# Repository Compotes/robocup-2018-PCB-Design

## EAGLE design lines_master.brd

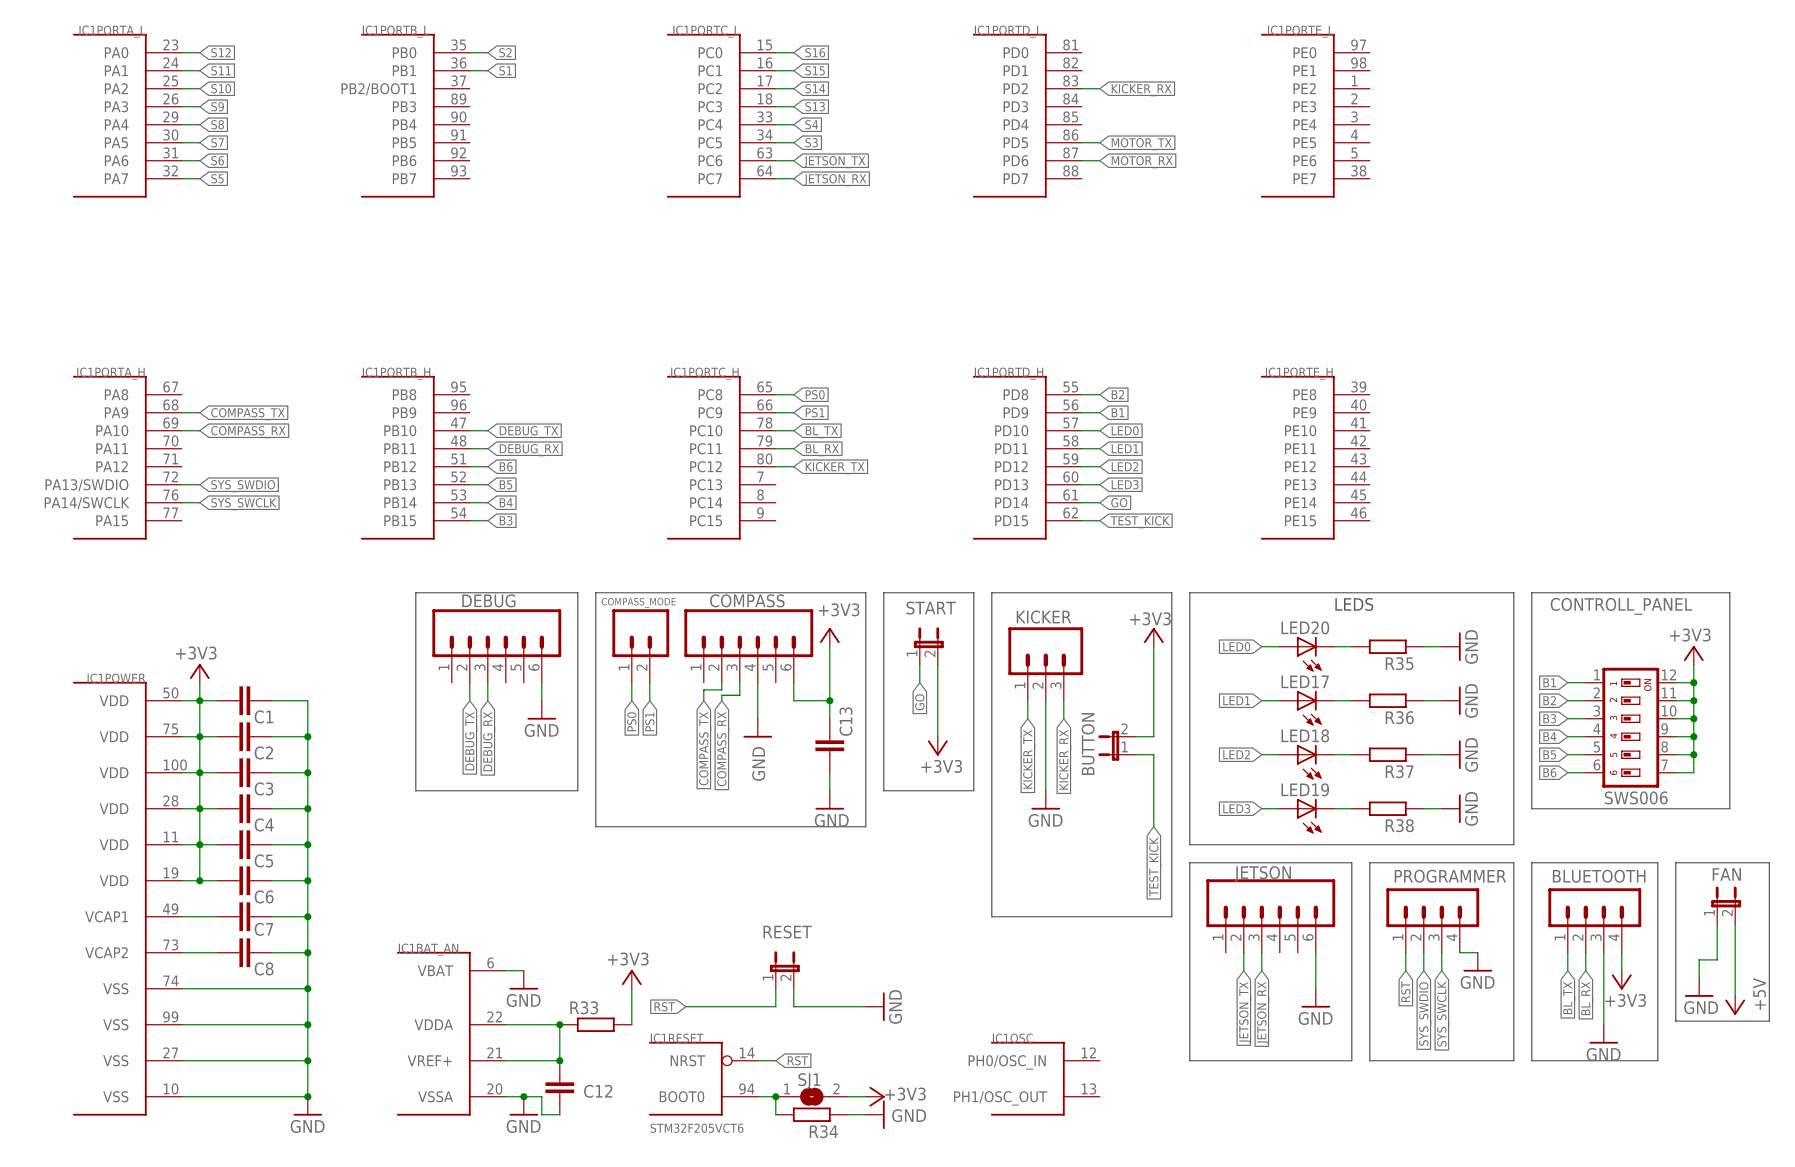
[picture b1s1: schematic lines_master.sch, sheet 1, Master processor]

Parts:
BLUETOOTH: MA04-1
BUTTON: JP1E; JP1
C1, C2, C3, C4, C5, C6, C12, C13: 100K; C0603
C7, C8: 2M2; C0805
COMPASS: M06; 06P
COMPASS_MODE: M02; 02P
CONTROLL_PANEL: SWS006; SMS-006
DEBUG: M06; 06P
FAN: JP1E; JP1
IC1: STM32F205VCT6; TQFP100
JETSON: M06; 06P
KICKER: M03; 03P
LED17, LED18, LED19, LED20: LED_E; LED_1206
PROGRAMMER: MA04-1
R33: R-EU_R1206; R1206
R34, R35, R36, R37, R38: R-EU_R0603; R0603
RESET: JP1E; JP1
SJ1: SJ
START: JP1E; JP1

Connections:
+3V3: BLUETOOTH.4, BUTTON.2, C1.2, C2.2, C3.2, C4.2, C5.2, C6.2, C13.1, COMPASS.6, CONTROLL_PANEL.7, CONTROLL_PANEL.8, CONTROLL_PANEL.9, CONTROLL_PANEL.10, CONTROLL_PANEL.11, CONTROLL_PANEL.12, IC1.11 (VDD), IC1.19 (VDD), IC1.28 (VDD), IC1.50 (VDD), IC1.75 (VDD), IC1.100 (VDD), R33.2, SJ1.2, START.2; also elsewhere on the board
+5V: FAN.2; also elsewhere on the board
B1: CONTROLL_PANEL.1, IC1.56 (PD9)
B2: CONTROLL_PANEL.2, IC1.55 (PD8)
B3: CONTROLL_PANEL.3, IC1.54 (PB15)
B4: CONTROLL_PANEL.4, IC1.53 (PB14)
B5: CONTROLL_PANEL.5, IC1.52 (PB13)
B6: CONTROLL_PANEL.6, IC1.51 (PB12)
BL_RX: BLUETOOTH.2, IC1.79 (PC11)
BL_TX: BLUETOOTH.1, IC1.78 (PC10)
COMPASS_RX: COMPASS.3, IC1.69 (PA10)
COMPASS_TX: COMPASS.2, IC1.68 (PA9)
DEBUG_RX: DEBUG.3, IC1.48 (PB11)
DEBUG_TX: DEBUG.2, IC1.47 (PB10)
GND: BLUETOOTH.3, C1.1, C2.1, C3.1, C4.1, C5.1, C6.1, C7.1, C8.1, C12.2, C13.2, COMPASS.4, DEBUG.6, FAN.1, IC1.6 (VBAT), IC1.10 (VSS), IC1.20 (VSSA), IC1.27 (VSS), IC1.74 (VSS), IC1.99 (VSS), JETSON.6, KICKER.2, PROGRAMMER.4, R34.1, R35.1, R36.1, R37.1, R38.1, RESET.2; also elsewhere on the board
GO: IC1.61 (PD14), START.1
JETSON_RX: IC1.64 (PC7), JETSON.3
JETSON_TX: IC1.63 (PC6), JETSON.2
KICKER_RX: IC1.83 (PD2), KICKER.3
KICKER_TX: IC1.80 (PC12), KICKER.1
LED0: IC1.57 (PD10), LED20.A
LED1: IC1.58 (PD11), LED17.A
LED2: IC1.59 (PD12), LED18.A
LED3: IC1.60 (PD13), LED19.A
MOTOR_RX: IC1.87 (PD6); also elsewhere on the board
MOTOR_TX: IC1.86 (PD5); also elsewhere on the board
unnamed: C7.2, IC1.49 (VCAP1)
unnamed: C8.2, IC1.73 (VCAP2)
unnamed: C12.1, IC1.21 (VREF+), IC1.22 (VDDA), R33.1
unnamed: IC1.94 (BOOT0), R34.2, SJ1.1
unnamed: LED20.C, R35.2
unnamed: LED17.C, R36.2
unnamed: LED18.C, R37.2
unnamed: LED19.C, R38.2
PS0: COMPASS_MODE.1, IC1.65 (PC8)
PS1: COMPASS_MODE.2, IC1.66 (PC9)
RST: IC1.14 (NRST), PROGRAMMER.1, RESET.1
S1: IC1.36 (PB1); also elsewhere on the board
S2: IC1.35 (PB0); also elsewhere on the board
S3: IC1.34 (PC5); also elsewhere on the board
S4: IC1.33 (PC4); also elsewhere on the board
S5: IC1.32 (PA7); also elsewhere on the board
S6: IC1.31 (PA6); also elsewhere on the board
S7: IC1.30 (PA5); also elsewhere on the board
S8: IC1.29 (PA4); also elsewhere on the board
S9: IC1.26 (PA3); also elsewhere on the board
S10: IC1.25 (PA2); also elsewhere on the board
S11: IC1.24 (PA1); also elsewhere on the board
S12: IC1.23 (PA0); also elsewhere on the board
S13: IC1.18 (PC3); also elsewhere on the board
S14: IC1.17 (PC2); also elsewhere on the board
S15: IC1.16 (PC1); also elsewhere on the board
S16: IC1.15 (PC0); also elsewhere on the board
SYS_SWCLK: IC1.76 (PA14/SWCLK), PROGRAMMER.3
SYS_SWDIO: IC1.72 (PA13/SWDIO), PROGRAMMER.2
TEST_KICK: BUTTON.1, IC1.62 (PD15)

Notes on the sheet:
LEDS

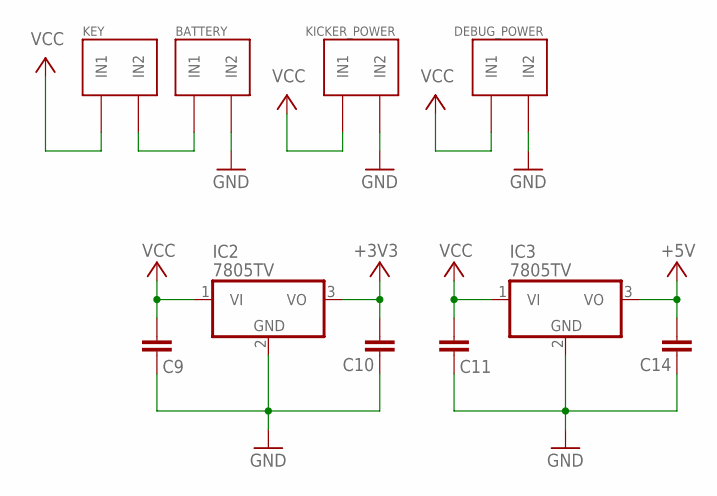
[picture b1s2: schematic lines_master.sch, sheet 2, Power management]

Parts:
BATTERY: MOTOR_CONNECTOR
C9, C10, C11, C14: 100K; C0603
DEBUG_POWER: MOTOR_CONNECTOR
IC2, IC3: 7805TV; TO220V
KEY: MOTOR_CONNECTOR
KICKER_POWER: MOTOR_CONNECTOR

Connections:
+3V3: C10.2, IC2.3 (VO); also elsewhere on the board
+5V: C14.2, IC3.3 (VO); also elsewhere on the board
GND: BATTERY.IN2, C9.1, C10.1, C11.1, C14.1, DEBUG_POWER.IN2, IC2.2 (GND), IC3.2 (GND), KICKER_POWER.IN2; also elsewhere on the board
unnamed: BATTERY.IN1, KEY.IN2
VCC: C9.2, C11.2, DEBUG_POWER.IN1, IC2.1 (VI), IC3.1 (VI), KEY.IN1, KICKER_POWER.IN1; also elsewhere on the board

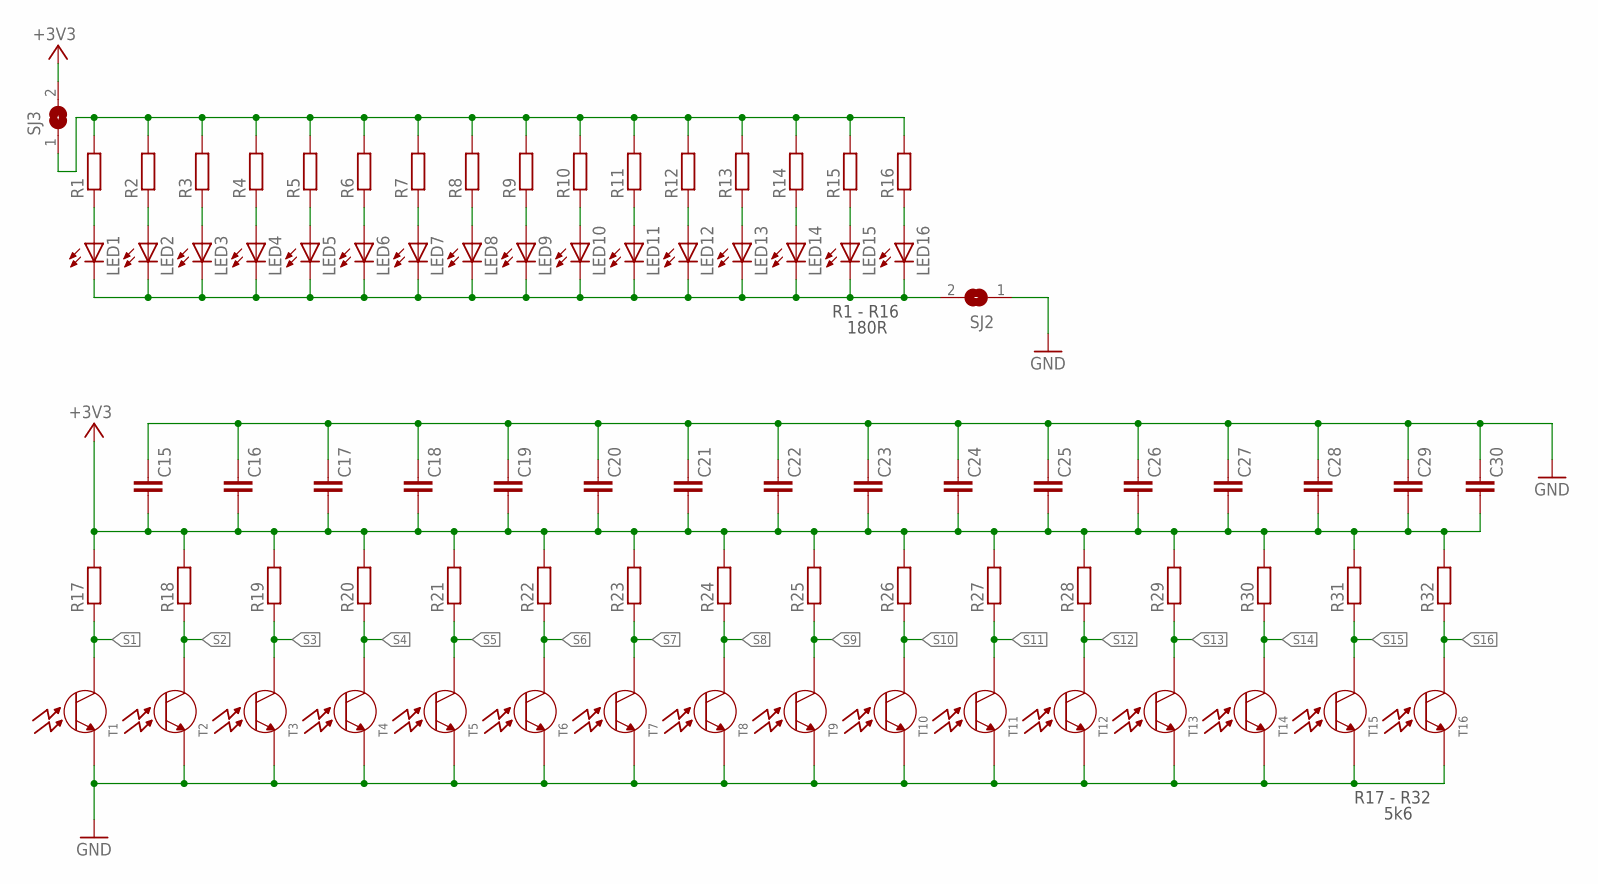
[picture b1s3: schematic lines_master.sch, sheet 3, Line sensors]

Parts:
C15, C16, C17, C18, C19, C20, C21, C22, C23, C24, C25, C26, C27, C28, C29, C30: 100K; C0603
LED1, LED2, LED3, LED4, LED5, LED6, LED7, LED8, LED9, LED10, LED11, LED12, LED13, LED14, LED15, LED16: LEDKA-3528ASYC; KA-3528ASYC
R1, R2, R3, R4, R5, R6, R7, R8, R9, R10, R11, R12, R13, R14, R15, R16: 180R; R0603
R17, R18, R19, R20, R21, R22, R23, R24, R25, R26, R27, R28, R29, R30, R31, R32: 5K6; R0603
SJ2, SJ3: SJ
T1, T2, T3, T4, T5, T6, T7, T8, T9, T10, T11, T12, T13, T14, T15, T16: LL-S150-1A; LL-S150PTC-1A

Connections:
+3V3: C15.2, C16.2, C17.2, C18.2, C19.2, C20.2, C21.2, C22.2, C23.2, C24.2, C25.2, C26.2, C27.2, C28.2, C29.2, C30.2, R17.2, R18.2, R19.2, R20.2, R21.2, R22.2, R23.2, R24.2, R25.2, R26.2, R27.2, R28.2, R29.2, R30.2, R31.2, R32.2, SJ3.2; also elsewhere on the board
GND: C15.1, C16.1, C17.1, C18.1, C19.1, C20.1, C21.1, C22.1, C23.1, C24.1, C25.1, C26.1, C27.1, C28.1, C29.1, C30.1, SJ2.1, T1.E, T2.E, T3.E, T4.E, T5.E, T6.E, T7.E, T8.E, T9.E, T10.E, T11.E, T12.E, T13.E, T14.E, T15.E, T16.E; also elsewhere on the board
unnamed: LED1.A, R1.1
unnamed: LED2.A, R2.1
unnamed: LED3.A, R3.1
unnamed: LED4.A, R4.1
unnamed: LED5.A, R5.1
unnamed: LED6.A, R6.1
unnamed: LED7.A, R7.1
unnamed: LED8.A, R8.1
unnamed: LED9.A, R9.1
unnamed: LED10.A, R10.1
unnamed: LED11.A, R11.1
unnamed: LED12.A, R12.1
unnamed: LED13.A, R13.1
unnamed: LED14.A, R14.1
unnamed: LED15.A, R15.1
unnamed: LED16.A, R16.1
unnamed: LED1.C, LED2.C, LED3.C, LED4.C, LED5.C, LED6.C, LED7.C, LED8.C, LED9.C, LED10.C, LED11.C, LED12.C, LED13.C, LED14.C, LED15.C, LED16.C, SJ2.2
unnamed: R1.2, R2.2, R3.2, R4.2, R5.2, R6.2, R7.2, R8.2, R9.2, R10.2, R11.2, R12.2, R13.2, R14.2, R15.2, R16.2, SJ3.1
S1: R17.1, T1.C; also elsewhere on the board
S2: R18.1, T2.C; also elsewhere on the board
S3: R19.1, T3.C; also elsewhere on the board
S4: R20.1, T4.C; also elsewhere on the board
S5: R21.1, T5.C; also elsewhere on the board
S6: R22.1, T6.C; also elsewhere on the board
S7: R23.1, T7.C; also elsewhere on the board
S8: R24.1, T8.C; also elsewhere on the board
S9: R25.1, T9.C; also elsewhere on the board
S10: R26.1, T10.C; also elsewhere on the board
S11: R27.1, T11.C; also elsewhere on the board
S12: R28.1, T12.C; also elsewhere on the board
S13: R29.1, T13.C; also elsewhere on the board
S14: R30.1, T14.C; also elsewhere on the board
S15: R31.1, T15.C; also elsewhere on the board
S16: R32.1, T16.C; also elsewhere on the board

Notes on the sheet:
R1 - R16 180R
R17 - R32 5k6

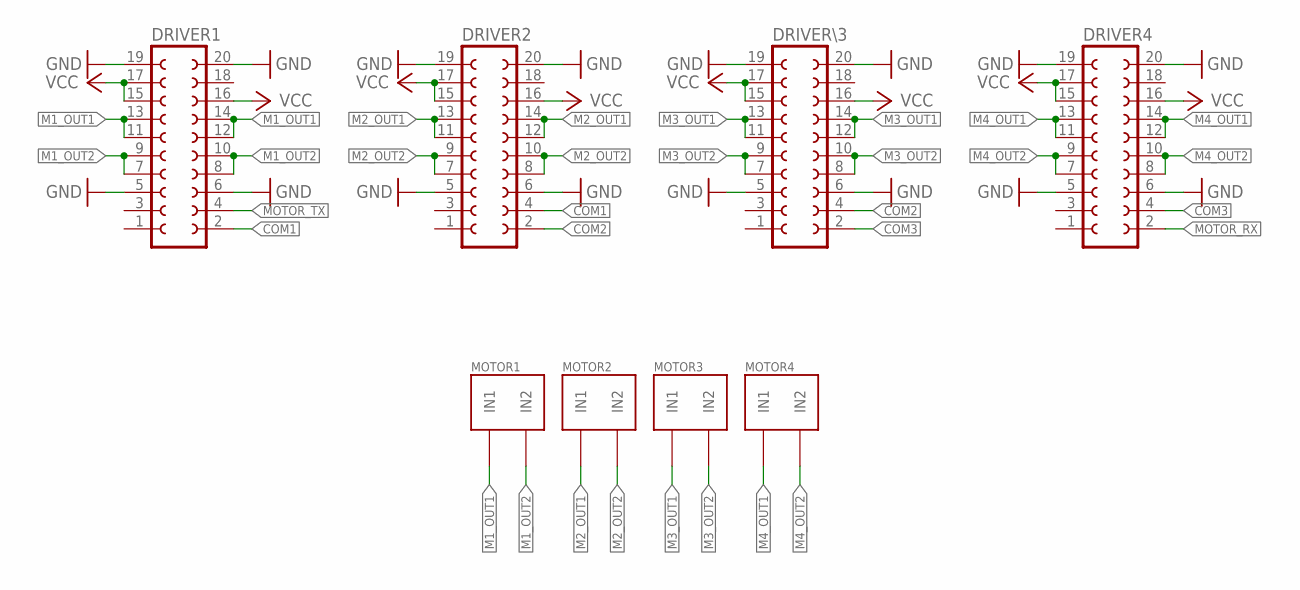
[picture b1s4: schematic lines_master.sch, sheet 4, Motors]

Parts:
DRIVER1, DRIVER2, DRIVER4: FE10-2
DRIVER\3: FE10-2
MOTOR1, MOTOR2, MOTOR3, MOTOR4: MOTOR_CONNECTOR

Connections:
COM1: DRIVER1.2, DRIVER2.4
COM2: DRIVER2.2, DRIVER\3.4
COM3: DRIVER4.4, DRIVER\3.2
GND: DRIVER1.5, DRIVER1.6, DRIVER1.19, DRIVER1.20, DRIVER2.5, DRIVER2.6, DRIVER2.19, DRIVER2.20, DRIVER4.5, DRIVER4.6, DRIVER4.19, DRIVER4.20, DRIVER\3.5, DRIVER\3.6, DRIVER\3.19, DRIVER\3.20; also elsewhere on the board
M1_OUT1: DRIVER1.11, DRIVER1.12, DRIVER1.13, DRIVER1.14, MOTOR1.IN1
M1_OUT2: DRIVER1.7, DRIVER1.8, DRIVER1.9, DRIVER1.10, MOTOR1.IN2
M2_OUT1: DRIVER2.11, DRIVER2.12, DRIVER2.13, DRIVER2.14, MOTOR2.IN1
M2_OUT2: DRIVER2.7, DRIVER2.8, DRIVER2.9, DRIVER2.10, MOTOR2.IN2
M3_OUT1: DRIVER\3.11, DRIVER\3.12, DRIVER\3.13, DRIVER\3.14, MOTOR3.IN1
M3_OUT2: DRIVER\3.7, DRIVER\3.8, DRIVER\3.9, DRIVER\3.10, MOTOR3.IN2
M4_OUT1: DRIVER4.11, DRIVER4.12, DRIVER4.13, DRIVER4.14, MOTOR4.IN1
M4_OUT2: DRIVER4.7, DRIVER4.8, DRIVER4.9, DRIVER4.10, MOTOR4.IN2
MOTOR_RX: DRIVER4.2; also elsewhere on the board
MOTOR_TX: DRIVER1.4; also elsewhere on the board
VCC: DRIVER1.15, DRIVER1.16, DRIVER1.17, DRIVER2.15, DRIVER2.16, DRIVER2.17, DRIVER4.15, DRIVER4.16, DRIVER4.17, DRIVER\3.15, DRIVER\3.16, DRIVER\3.17; also elsewhere on the board

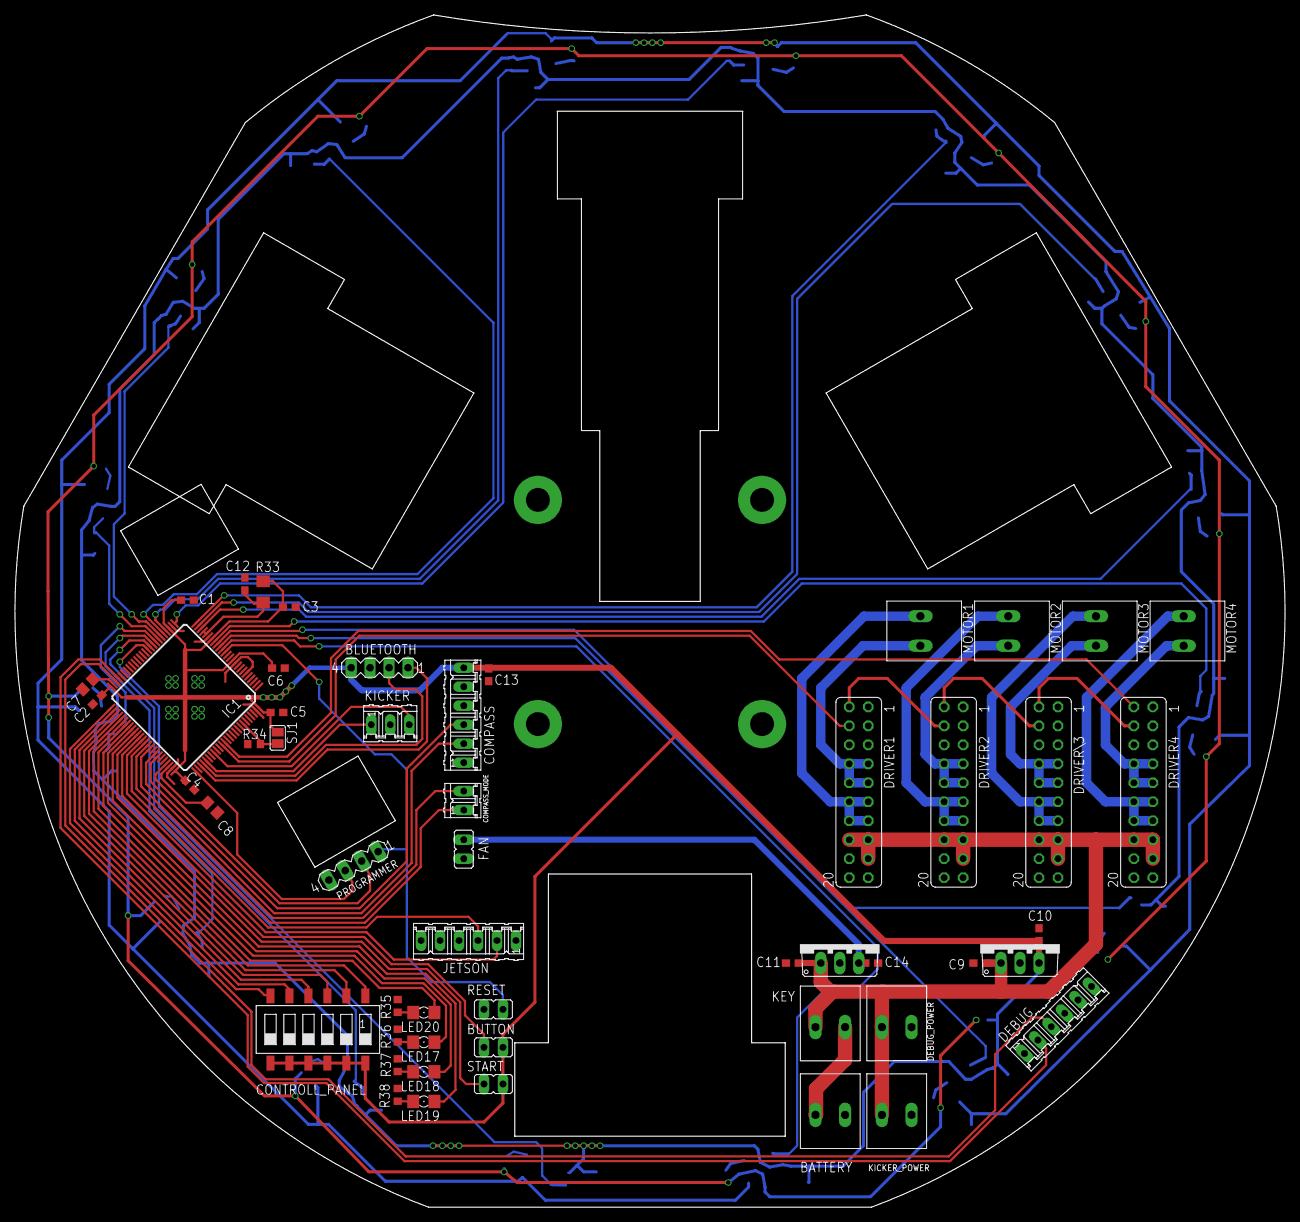
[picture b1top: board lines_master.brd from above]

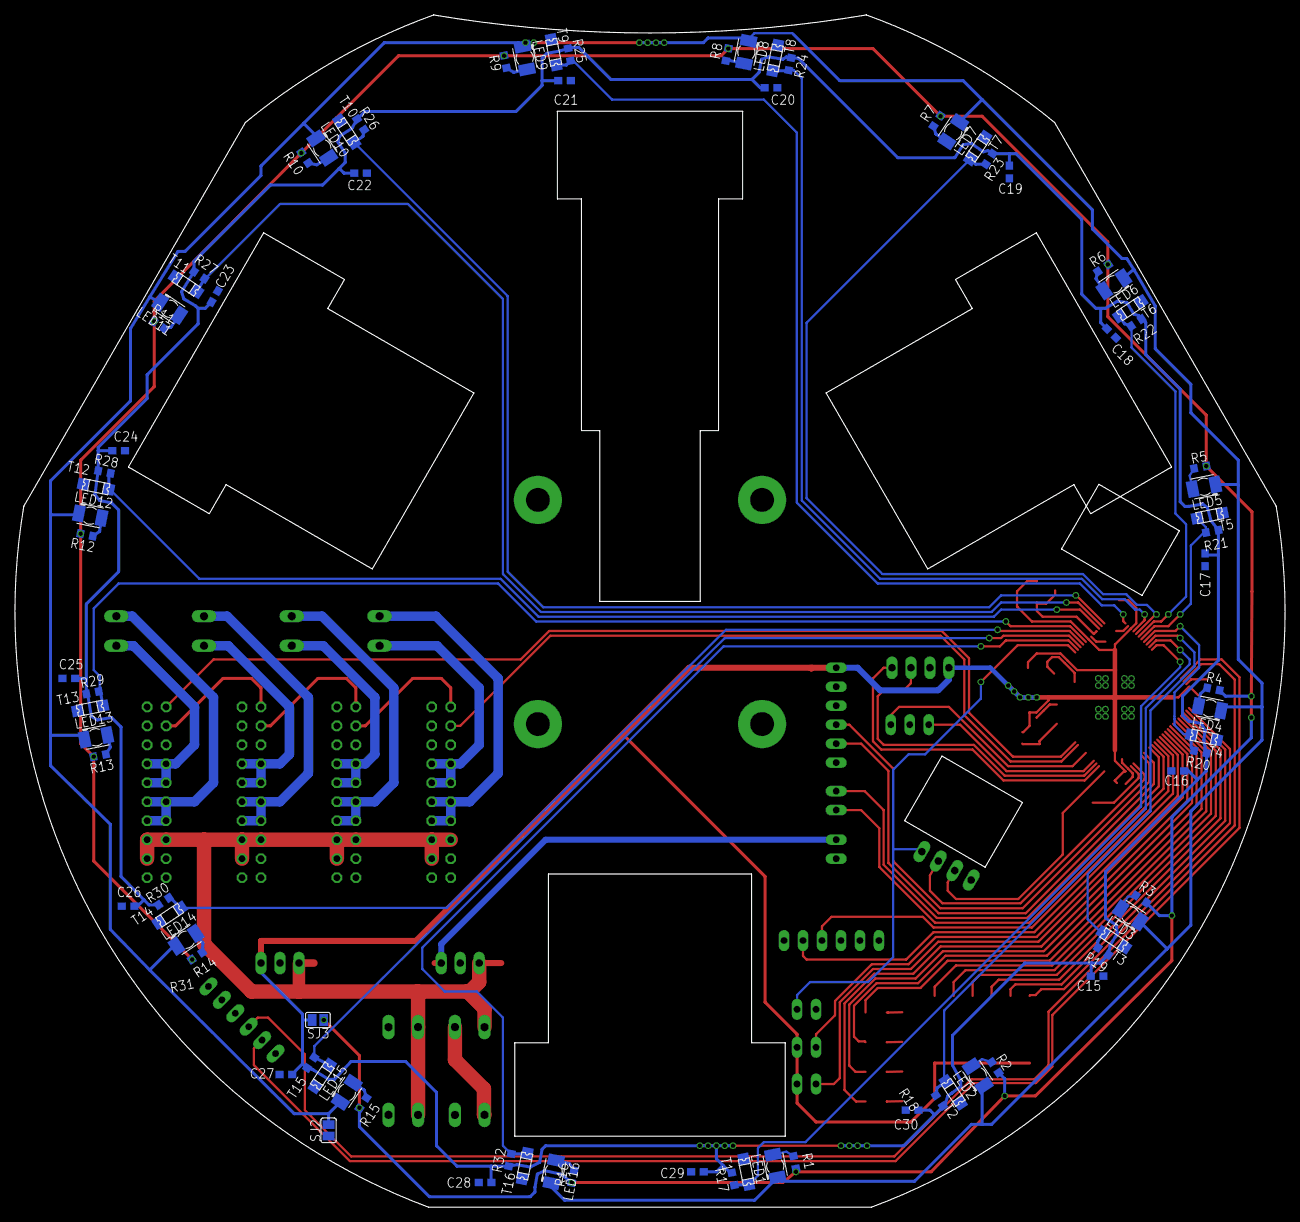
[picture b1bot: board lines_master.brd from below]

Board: 2 copper layers, 170.0 x 159.6 mm, 134 parts (82 on the bottom side), 87 nets.

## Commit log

2018-06-13 Add eagle files
